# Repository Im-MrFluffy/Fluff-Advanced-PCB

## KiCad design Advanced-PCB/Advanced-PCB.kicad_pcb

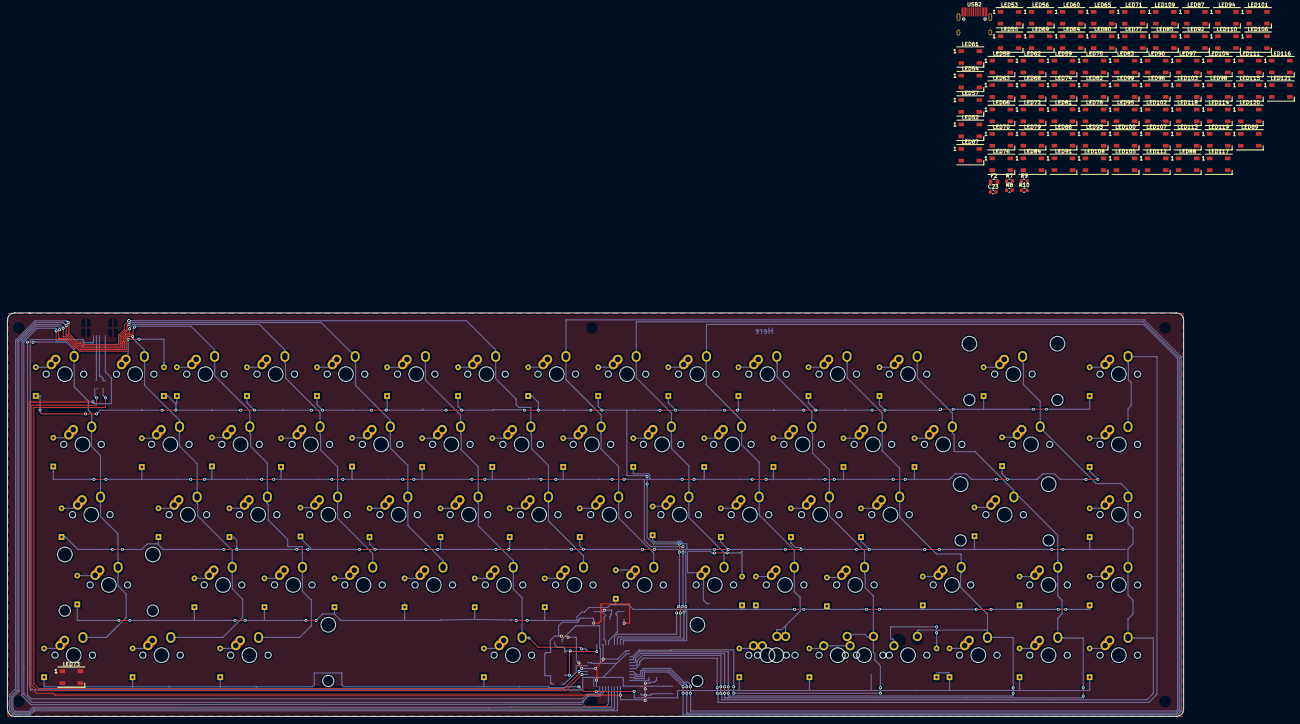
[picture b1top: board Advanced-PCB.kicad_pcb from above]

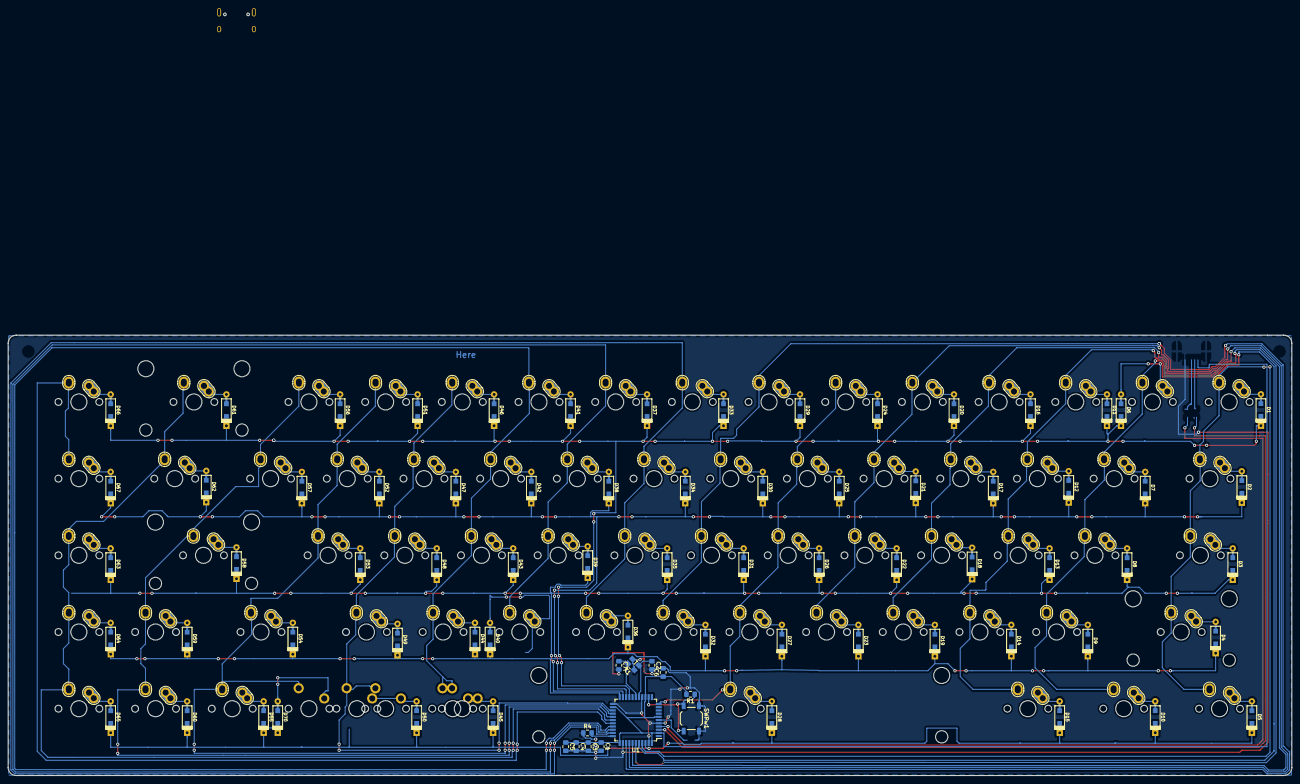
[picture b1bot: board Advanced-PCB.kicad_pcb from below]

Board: 2 copper layers, 318.9 x 109.4 mm, 227 parts (150 on the bottom side), 102 nets.

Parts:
C1, C3, C4, C5: .1u; C_0805_2012Metric_Pad1.15x1.40mm_HandSolder
C2, C7: 22pF; C_0805_2012Metric_Pad1.15x1.40mm_HandSolder
C6: 4.7u; C_0805_2012Metric_Pad1.15x1.40mm_HandSolder
C23: 1u; C_0603_1608Metric
D1, D2, D3, D4, D5, D6, D7, D8, D9, D10, D11, D12, D13, D14, D15, D16, D17, D18, D19, D20, D21, D22, D23, D24, D25, D26, D27, D28, D29, D30, D31, D32, D33, D34, D35, D36, D37, D38, D39, D40, D41, D42, D43, D44, D45, D46, D47, D48, D49, D50, D51, D52, D53, D54, D55, D56, D57, D58, D59, D60, D61, D62, D63, D64, D65, D66, D67, D70: 1N4148W; D_SOD123_axial
F2: 500mA; R_0805_2012Metric
LED52, LED53, LED54, LED55, LED56, LED57, LED58, LED59, LED60, LED61, LED62, LED63, LED64, LED65, LED66, LED67, LED68, LED69, LED70, LED71, LED72, LED73, LED74, LED75, LED76, LED77, LED78, LED79, LED80, LED81, LED82, LED83, LED84, LED85, LED86, LED87, LED88, LED89, LED90, LED91, LED92, LED93, LED94, LED95, LED96, LED97, LED98, LED99, LED100, LED101, LED102, LED103, LED104, LED105, LED106, LED107, LED108, LED109, LED110, LED111, LED112, LED113, LED114, LED115, LED116, LED117, LED118, LED119, LED120, LED121: LED; LED_WS2812B_PLCC4_5.0x5.0mm_P3.2mm
R1, R4: 10k; R_0805_2012Metric_Pad1.15x1.40mm_HandSolder
R7, R8: 22; R_0603_1608Metric
R9, R10: 5.1k; R_0603_1608Metric
SW1: Esc; MXA100
SW2: Tab 1.50; MXA150
SW3: Caps 1.75; MXA175
SW4: Shift 2.25; MXA225R
SW5: Ctrl 1.25; MXA125
SW6: 1; MXA100
SW7: Q; MXA100
SW8: A; MXA100
SW9: Z; MXA100
SW10: Win 1.25; MXA125
SW11: 2; MXA100
SW12: W; MXA100
SW13: S; MXA100
SW14: X; MXA100
SW15: Alt 1.25; MXA125
SW16: 3; MXA100
SW17: E; MXA100
SW18: D; MXA100
SW19: C; MXA100
SW20: 4; MXA100
SW21: R; MXA100
SW22: F; MXA100
SW23: V; MXA100
SW24: 5; MXA100
SW25: T; MXA100
SW26: G; MXA100
SW27: B; MXA100
SW28: Space 6.25; MXA625R
SW29: 6; MXA100
SW30: Y; MXA100
SW31: H; MXA100
SW32: N; MXA100
SW33: 7; MXA100
SW34: U; MXA100
SW35: J; MXA100
SW36: M; MXA100
SW37: 8; MXA100
SW38: I; MXA100
SW39: K; MXA100
SW40: ,; MXA100
SW41: 9; MXA100
SW42: P; MXA100
SW43: L; MXA100
SW44: .; MXA100
SW45: Alt 1.25; MX125
SW46: 0; MXA100
SW47: O; MXA100
SW48: ;; MXA100
SW49: /; MXA100
SW50: Fn 1.25; MX125
SW51: -; MXA100
SW52: [; MXA100
SW53: '; MXA100
SW54: Shift 1.75; MXA175
SW55: Left Arrow; MXA100
SW56: =; MXA100
SW57: ]; MXA100
SW58: Enter 2.25; MXA225R
SW59: Up Arrow; MXA100
SW60: Down Arrow; MXA100
SW61: Back 2.00; MXA200R
SW62: \ 1.50; MXA150
SW63: Pg Up; MXA100
SW64: Pg Down; MXA100
SW65: Right Arrow; MXA100
SW66: `; MXA100
SW67: Del; MXA100
SW68: Alt 1.00; MX100
SW69: Fn 1.00; MX100
SW70: Ctrl 1.00; MX100
SWPw1: SW_PUSH; SW_SPST_TL3342
U1: ATMEGA32U4; TQFP-44_10x10mm_P0.8mm
USB2: HRO-TYPE-C-31-M-12; HRO-TYPE-C-31-M-12-HandSoldering
X1: XTAL_GND; crystal_FA238-TSX3225

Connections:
+5V: F2.1, U1.2, U1.7
Col1: SW1.1, SW2.1, SW3.1, SW4.1, SW5.1, U1.41
Col2: SW6.1, SW7.1, SW8.1, SW9.1, SW10.1, U1.40
Col3: SW11.1, SW12.1, SW13.1, SW14.1, SW15.1, U1.39
Col4: SW16.1, SW17.1, SW18.1, SW19.1, U1.38
Col5: SW20.1, SW21.1, SW22.1, SW23.1, U1.37
Col6: SW24.1, SW25.1, SW26.1, SW27.1, SW28.1, U1.11
Col7: SW29.1, SW30.1, SW31.1, SW32.1, U1.36
Col8: SW33.1, SW34.1, SW35.1, SW36.1, U1.32
Col9: SW37.1, SW38.1, SW39.1, SW40.1, U1.31
Col10: SW41.1, SW42.1, SW43.1, SW44.1, SW45.1, SW68.1, U1.30
Col11: SW46.1, SW47.1, SW48.1, SW49.1, SW50.1, SW69.1, U1.25
Col12: SW51.1, SW52.1, SW53.1, SW54.1, SW55.1, SW70.1, U1.26
Col13: SW56.1, SW57.1, SW58.1, SW59.1, SW60.1, U1.27
Col14: SW61.1, SW62.1, SW63.1, SW64.1, SW65.1, U1.28
Col15: SW66.1, SW67.1, U1.29
D+: R8.2, USB2.6, USB2.8
D-: R7.2, USB2.5, USB2.7
GND: C1.2, C2.2, C3.2, C4.2, C5.2, C6.2, C7.2, C23.2, R4.1, R9.1, R10.1, SWPw1.1, U1.5, U1.15, U1.23, U1.35, U1.43, USB2.1, USB2.12, USB2.13, X1.3
unnamed: C2.1, U1.16, X1.1
unnamed: C7.1, U1.17, X1.2
unnamed: C23.1, U1.6
unnamed: D1.2, SW1.2
unnamed: D2.2, SW2.2
unnamed: D3.2, SW3.2
unnamed: D4.2, SW4.2
unnamed: D5.2, SW5.2
unnamed: D6.2, SW6.2
unnamed: D7.2, SW7.2
unnamed: D8.2, SW8.2
unnamed: D9.2, SW9.2
unnamed: D10.2, SW10.2
unnamed: D11.2, SW11.2
unnamed: D12.2, SW12.2
unnamed: D13.2, SW13.2
unnamed: D14.2, SW14.2
unnamed: D15.2, SW15.2
unnamed: D16.2, SW16.2
unnamed: D17.2, SW17.2
unnamed: D18.2, SW18.2
unnamed: D19.2, SW19.2
unnamed: D20.2, SW20.2
unnamed: D21.2, SW21.2
unnamed: D22.2, SW22.2
unnamed: D23.2, SW23.2
unnamed: D24.2, SW24.2
unnamed: D25.2, SW25.2
unnamed: D26.2, SW26.2
unnamed: D27.2, SW27.2
unnamed: D28.2, SW28.2
unnamed: D29.2, SW29.2
unnamed: D30.2, SW30.2
unnamed: D31.2, SW31.2
unnamed: D32.2, SW32.2
unnamed: D33.2, SW33.2
unnamed: D34.2, SW34.2
unnamed: D35.2, SW35.2
unnamed: D36.2, SW36.2
unnamed: D37.2, SW37.2
unnamed: D38.2, SW38.2
unnamed: D39.2, SW39.2
unnamed: D40.2, SW40.2
unnamed: D41.2, SW41.2
unnamed: D42.2, SW42.2
unnamed: D43.2, SW43.2
unnamed: D44.2, SW44.2
unnamed: D45.2, SW45.2, SW68.2
unnamed: D46.2, SW46.2
unnamed: D47.2, SW47.2
unnamed: D48.2, SW48.2
unnamed: D49.2, SW49.2
unnamed: D50.2, SW50.2, SW69.2
unnamed: D51.2, SW51.2
unnamed: D52.2, SW52.2
unnamed: D53.2, SW53.2
unnamed: D54.2, SW54.2
unnamed: D55.2, SW55.2
unnamed: D56.2, SW56.2
unnamed: D57.2, SW57.2
unnamed: D58.2, SW58.2
unnamed: D59.2, SW59.2
unnamed: D60.2, SW60.2
unnamed: D61.2, SW61.2
unnamed: D62.2, SW62.2
unnamed: D63.2, SW63.2
unnamed: D64.2, SW64.2
unnamed: D65.2, SW65.2
unnamed: D66.2, SW66.2
unnamed: D67.2, SW67.2
unnamed: D70.2, SW70.2
unnamed: R1.1, SWPw1.2, U1.13
unnamed: R4.2, U1.33
unnamed: R7.1, U1.3
unnamed: R8.1, U1.4
unnamed: R9.2, USB2.4
unnamed: R10.2, USB2.10
Row0: D5.1, D10.1, D15.1, D28.1, D45.1, D50.1, D55.1, D60.1, D65.1, D70.1, U1.18
Row1: D4.1, D9.1, D14.1, D19.1, D23.1, D27.1, D32.1, D36.1, D40.1, D44.1, D49.1, D54.1, D59.1, D64.1, U1.22
Row2: D3.1, D8.1, D13.1, D18.1, D22.1, D26.1, D31.1, D35.1, D39.1, D43.1, D48.1, D53.1, D58.1, D63.1, U1.21
Row3: D2.1, D7.1, D12.1, D17.1, D21.1, D25.1, D30.1, D34.1, D38.1, D42.1, D47.1, D52.1, D57.1, D62.1, D67.1, U1.20
Row4: D1.1, D6.1, D11.1, D16.1, D20.1, D24.1, D29.1, D33.1, D37.1, D41.1, D46.1, D51.1, D56.1, D61.1, D66.1, U1.19
VCC: C1.1, C3.1, C4.1, C5.1, C6.1, F2.2, R1.2, U1.14, U1.24, U1.34, U1.44, USB2.2, USB2.11

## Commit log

2020-03-06 Components and Footprints Added
    Components and Footprints Added and PCB started.
2020-03-06 First Row Added
    First Row added to layout and keycaps labeled.
2020-03-06 Second Row Added
    Second Row added to Matrix and Labeled.
2020-03-06 KB Layout Finished
    All KB rows and columns and labels added.
2020-03-06 Corrections and Fixes to Full Matrix
    Full matrix completed and all wires and junctions connected properly, and all labels attached.
2020-03-06 Bottom Row Re-Alligned
    Bottom Row Realigned to help with Trace in later steps.
2020-03-06 KB Sizes Added
    Non 1u switches sizes added to label.
2020-03-07 Key Dimensions Corrected
    All keys have the correct lenght and hot swap profile. Switches larger than 2u have north facing stabs.
2020-03-07 PCB Layout Complete
    Full PCB layed out in wanted order.
2020-03-07 Alternate Row 0
    Alternate Row zero with 1u right side keys added.
2020-03-07 Layout Simplified
    Layout Simplified by stacking switches unable to be used at same time because of different kb layouts. Right alt and fn with ctrl left down as seperate row.
2020-03-07 Rows And Columns Fixed
    Fixed Issue to make all columns and rows linked properly
2020-03-08 Mid Routing
    In the Middle of Routing. All of tracing between initial components done. Switches still need to be traced and connected.
2020-03-08 Traces Continued
    Continued Tracing All Rows and Half Columns completed.
2020-03-09 PCB-Rerouted
    Correctly Rerouted and except of errors except for with layer keys.
2020-06-17 BACKUP
